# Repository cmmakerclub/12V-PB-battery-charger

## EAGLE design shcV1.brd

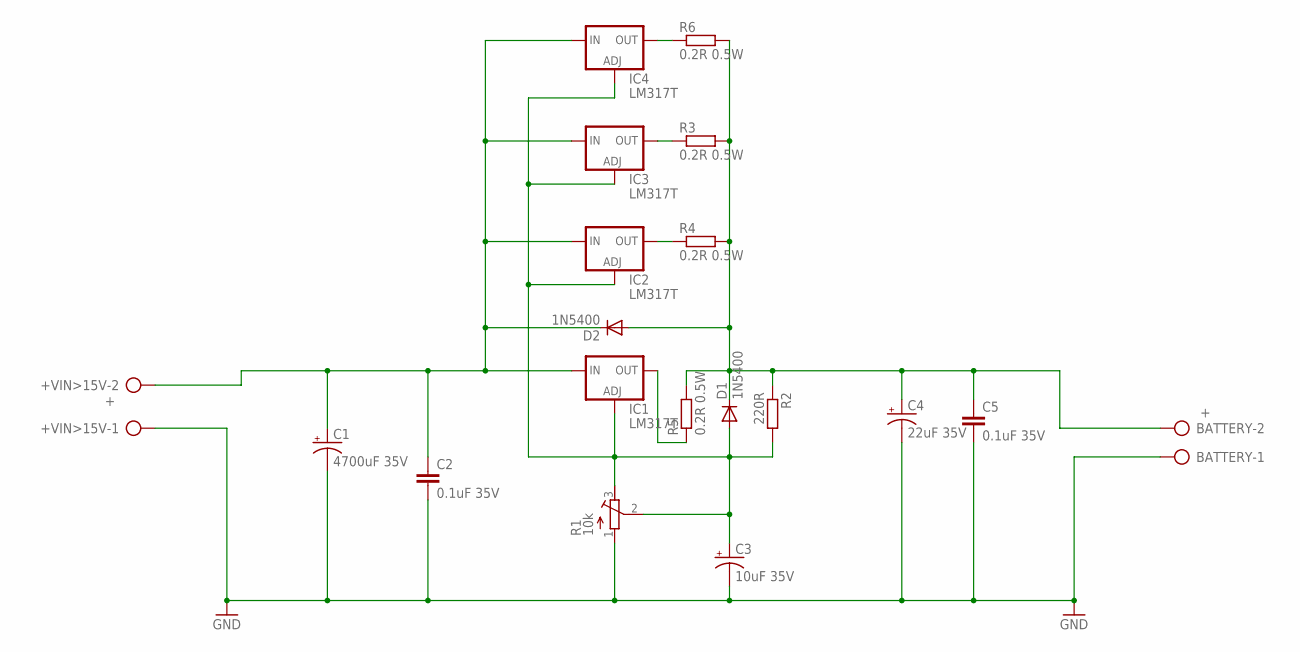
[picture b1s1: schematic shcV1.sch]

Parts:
+VIN>15V: +; AK300/2
BATTERY: +; AK300/2
C1: 4700uF 35V; E5-13
C2, C5: 0.1uF 35V; C050-024X044
C3: 10uF 35V; E5-13
C4: 22uF 35V; E5-13
D1, D2: 1N5400; DO201-15
IC1, IC2, IC3, IC4: LM317T; 317TS
R1: 10k; RTRIM64W
R2: 220R; 0207/10
R3, R4, R5, R6: 0.2R 0.5W; 0207/10

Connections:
+BATTERY12V: BATTERY.2, C4.+, C5.1, D1.C, D2.A, R2.1, R3.2, R4.2, R5.2, R6.2
+FROM_MPPT: +VIN>15V.2, C1.+, C2.1, D2.C, IC1.3 (IN), IC2.3 (IN), IC3.3 (IN), IC4.3 (IN)
GND: +VIN>15V.1, BATTERY.1, C1.-, C2.2, C3.-, C4.-, C5.2, R1.1 (A)
unnamed: IC4.2 (OUT), R6.1
unnamed: C3.+, D1.A, IC1.1 (ADJ), IC2.1 (ADJ), IC3.1 (ADJ), IC4.1 (ADJ), R1.2 (S), R1.3 (E), R2.2
unnamed: IC1.2 (OUT), R5.1
unnamed: IC3.2 (OUT), R3.1
unnamed: IC2.2 (OUT), R4.1

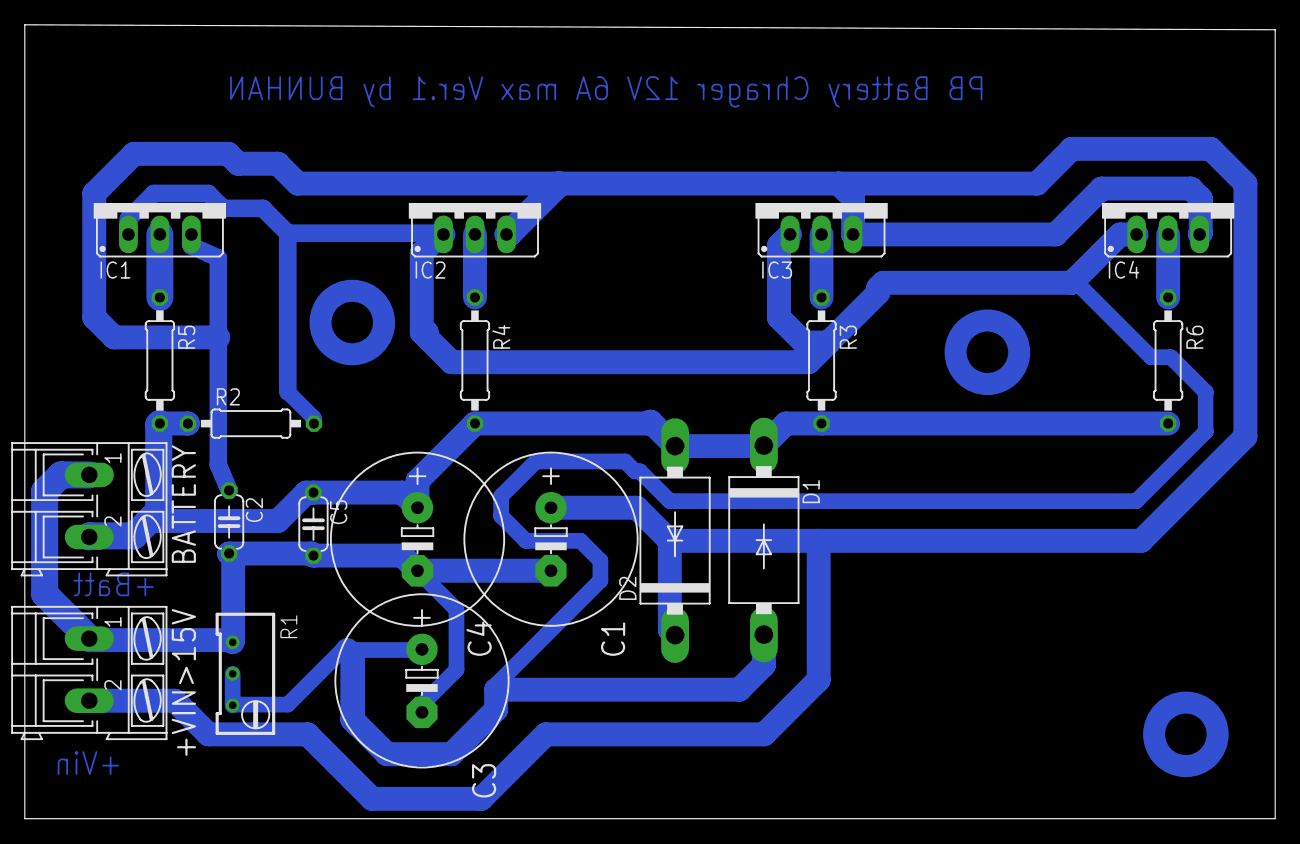
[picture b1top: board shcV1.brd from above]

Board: 2 copper layers, 100.8 x 64.0 mm, 19 parts (0 on the bottom side), 8 nets.

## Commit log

2015-06-12 Crete ver. 1.0
2015-06-12 Add comment in shc
2015-06-12 Add PCB.pdf
